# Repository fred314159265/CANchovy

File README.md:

# CANchovy USB-CAN Interface

This repository contains the design file for an isolated USB-CAN interface PCB. It is based upon the MKS CANable V2.0 and is compatible with the [CANable V2.0 firmware](https://github.com/normaldotcom/canable2-fw). It connects to the CAN bus via RJ45 connectors which can be configured with whatever pinout you require!

## Features

* Firmware compatible with [CANable V2.0 firmware](https://github.com/normaldotcom/canable2-fw) - can be flashed & updated with the [CANable 2.0 web updater](https://canable.io/updater/canable2.html).
* RJ45 pinout configured via solder-able jumpers.
* Galvanic isolation between CAN port and USB.
* Two RJ45 connector in parallel allows for inserting inline on bus - all eight signal are passed through.
* DIP switch to enable or disable CAN termination.
* DIP switch to enable silent mode, preventing the CANchovy from transmitting on the bus in hardware.
* JLCPCB basic parts used where possible and all parts available for JLCPCB assembly service. Five CANchovies fully assembled with postage costs around $20 per CANchovy.
* 3D printed case design files.

# Status

Assembled CANchovies from JLCPCB of both revision A & B have been tested and work correctly. The only issues with these version were silkscreen issues.

Revision C has the silkscreen fixed and is ready to manufacture and use.

# Firmware

As the CANchovy is based upon the MKS CANable V2.0, it is compatible with firmware which is compatible with the MKS CANable V2.0.

There area couple of suitable firmware options - which firmware you will want to use really depends on your use case. 

## gs_usb

Using a firmware version which uses the gs_usb protocol will mostly be useful for SocketCAN on Linux, but [python-can](https://python-can.readthedocs.io/en/stable/interfaces/gs_usb.html) does support the gs_usb protocol on all platforms. (__Note:__ The Linux kernel only supports CAN FD with the gs_usb driver after version 5.18.)

* budgetcan_fw - [board_canablev2](https://github.com/ryedwards/budgetcan_fw/tree/main/Portable/board_canablev2) target - I have confirmed that FD CAN is working as of [`e8fb8efebdac22019dc7e73dfec773c6fd2ec5a8`](https://github.com/ryedwards/budgetcan-fw/commit/e8fb8efebdac22019dc7e73dfec773c6fd2ec5a8).
* candlelight build from [CANable 2.0 web updater](https://canable.io/updater/canable2.html) - I have not tested if FD CAN support is present, notes on canable website suggest FD support is not implemented in these candlelight FW builds (yet?).

## SLCAN

SLCAN is a protocol which operates over a serial port. Nearly all OS's have support for serial ports and so is very cross-platform. However, support for SLCAN is not very widespread.

You can also mount the serial port as a SocketCAN port on Linux (E.g. as described [here](https://elinux.org/Bringing_CAN_interface_up).), however, it does not support FD CAN at this time.

FD CAN is possible with the SLCAN firmware, but even fewer programs support FD with SLCAN (if any?). It may be a viable for custom applications where non-Linux is a requirement and Python is not an option.

* slcan with FD support build from [CANable 2.0 web updater](https://canable.io/updater/canable2.html) - [source repo](https://github.com/normaldotcom/canable2-fw).

# Configuring RJ45 Connections

As mentioned above, a feature of this board is that the RJ45's pinout is user configurable. By soldering one jumper for each of the three connections (0V, CAN_H, CAN_L) on the rear of the board, your custom CAN pinout over RJ45 can be supported!

Simply bridge one of the solder jumpers in each of the silkscreen boxes (labelled: 0V, CAN_H & CAN_L) to connect each signal to the corresponding pin number of the RJ45 connectors.

__⚠⚠⚠ Care must be taken to ensure no two signals are connected to the same RJ45 pin! ⚠⚠⚠__

# Ordering

Gerbers, BOM, etc. can all be found in the [releases](https://github.com/fred314159265/CANchovy/releases) area.

When ordering from JLCPCB, is is suggested to select "JLC04161H-7628" under the controlled impedance option, although the USB run is so short that even non-controlled impedance stack-ups will likely work too.

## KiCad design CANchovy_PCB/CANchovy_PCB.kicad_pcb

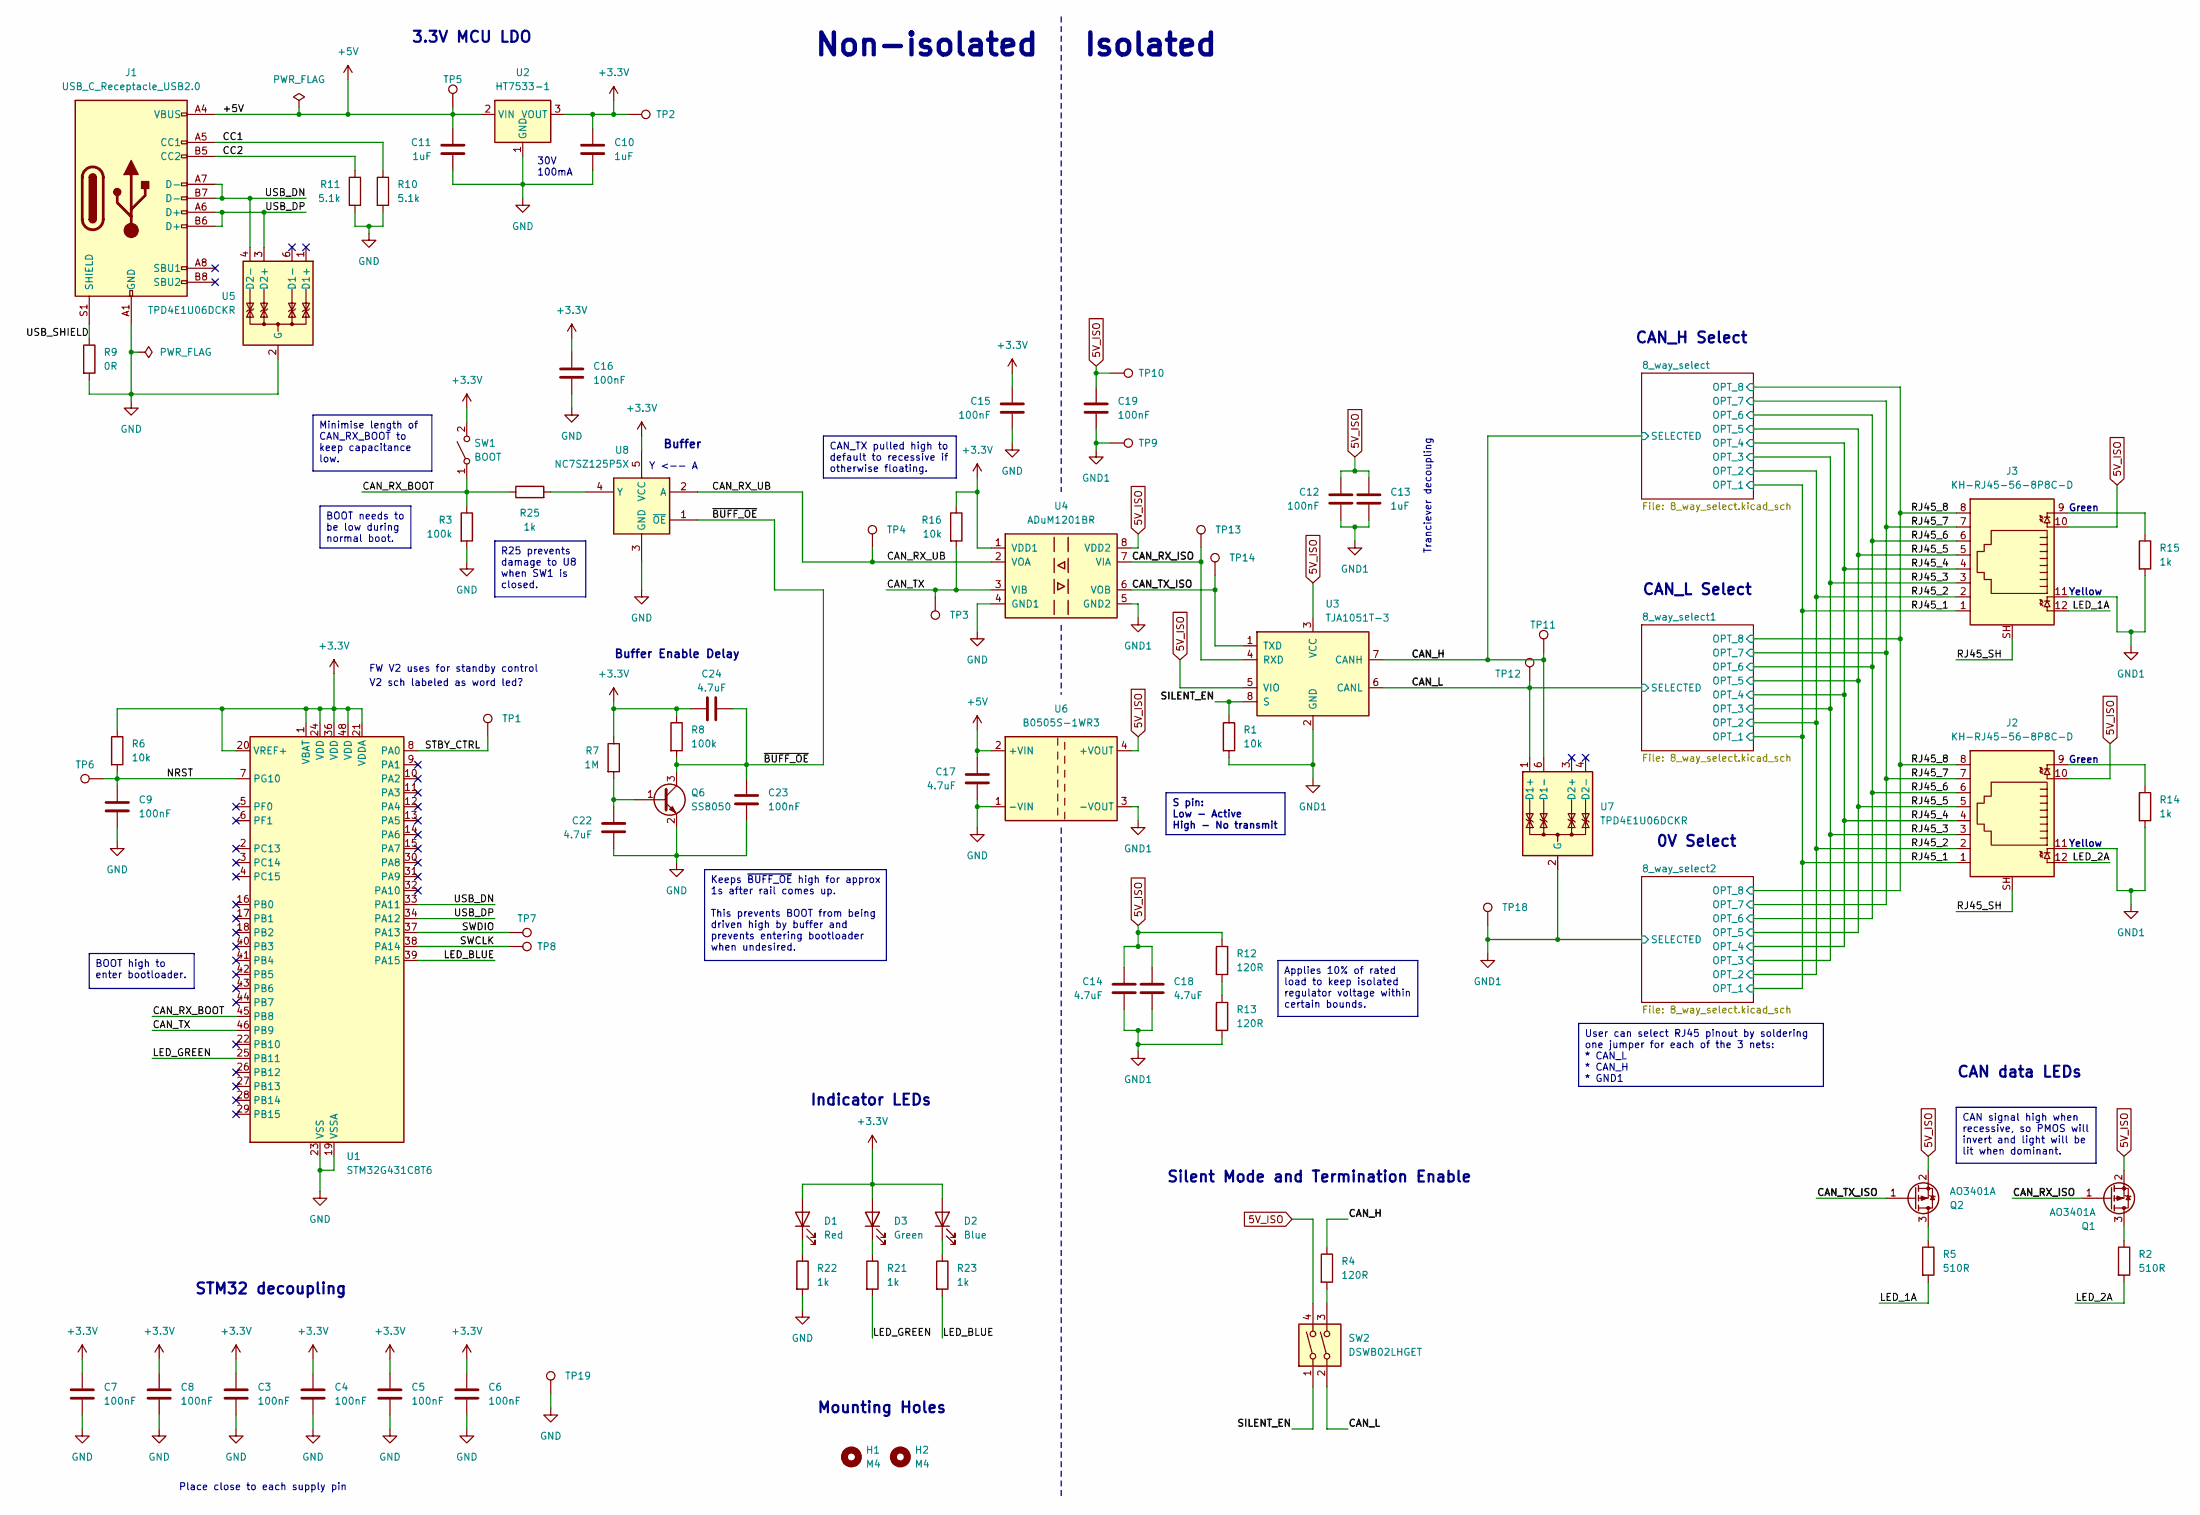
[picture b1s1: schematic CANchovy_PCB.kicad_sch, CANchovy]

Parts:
C3, C4, C5, C6, C7, C8, C9, C12, C15, C16, C19, C23: 100nF; C_0603_1608Metric; Manufacturer Part # CC0603KRX7R9BB104; LCSC Part # C14663
C10, C11, C13: 1uF; C_0805_2012Metric; Manufacturer Part # CL21B105KBFNNNE; LCSC Part # C28323
C14, C17, C18, C22, C24: 4.7uF; C_0805_2012Metric; Manufacturer Part # CL21A475KAQNNNE; LCSC Part # C1779
D1: Red; LED_0603_1608Metric; Manufacturer Part # KT-0603R; LCSC Part # C2286
D2: Blue; LED_0603_1608Metric; Manufacturer Part # XL-1608UBC-04; LCSC Part # C965807
D3: Green; LED_0603_1608Metric; Manufacturer Part # XL-1608UGC-04; LCSC Part # C965804
H1, H2: M4; MountingHole_4.3mm_M4
J1: USB_C_Receptacle_USB2.0; USB_C_Receptacle_XKB_U262-16XN-4BVC11; Manufacturer Part # U262-161N-4BVC11; LCSC Part # C319148
J2, J3: KH-RJ45-56-8P8C-D; Manufacturer Part # KH-RJ45-56-8P8C-D; LCSC Part # C2828082
Q1, Q2: AO3401A; SOT-23; LCSC Part # C15127
Q6: SS8050; SOT-23; Manufacturer Part # SS8050; LCSC Part # C2150
R1, R6, R16: 10k; R_0603_1608Metric; Manufacturer Part # 0603WAF1002T5E; LCSC Part # C25804
R2, R5: 510R; R_0603_1608Metric; Manufacturer Part # 0603WAF5100T5E; LCSC Part # C23193
R3, R8: 100k; R_0603_1608Metric; Manufacturer Part # 0603WAF1003T5E; LCSC Part # C25803
R4, R12, R13: 120R; R_0603_1608Metric; Manufacturer Part # 0603WAF1200T5E; LCSC Part # C22787
R7: 1M; R_0603_1608Metric; Manufacturer Part # 0603WAF1004T5E; LCSC Part # C22935
R9: 0R; R_0603_1608Metric; Manufacturer Part # 0603WAF0000T5E; LCSC Part # C21189
R10, R11: 5.1k; R_0603_1608Metric; Manufacturer Part # 0603WAF5101T5E; LCSC Part # C23186
R14, R15, R21, R22, R23, R25: 1k; R_0603_1608Metric; Manufacturer Part # 0603WAF1001T5E; LCSC Part # C21190
SW1: BOOT; SW_Push_1P1T_XKB_TS-1187A; Manufacturer Part # TS-1187A-B-A-B; LCSC Part # C318884
SW2: DSWB02LHGET; SW_DIP_SPSTx02_Slide_9.78x7.26mm_W7.62mm_P2.54mm; Manufacturer Part # DSWB02LHGET; LCSC Part # C99421
TP1, TP2, TP3, TP4, TP5, TP6, TP7, TP8, TP9, TP10, TP11, TP12, TP13, TP14, TP18, TP19: TestPoint; TestPoint_THTPad_1.0x1.0mm_Drill0.5mm
U1: STM32G431C8T6; LQFP-48_7x7mm_P0.5mm; Manufacturer Part # STM32G431C8T6; LCSC Part # C730096
U2: HT7533-1; SOT-89-3; Manufacturer Part # HT7533-1; LCSC Part # C14289
U3: TJA1051T-3; SOIC-8_3.9x4.9mm_P1.27mm; Manufacturer Part # TJA1051T/3/1J; LCSC Part # C38695
U4: ADuM1201BR; SOIC-8_3.9x4.9mm_P1.27mm; Manufacturer Part # ADUM1201BRZ-RL7; LCSC Part # C87626
U5, U7: TPD4E1U06DCKR; SOT-363_SC-70-6; LCSC Part # C194628
U6: B0505S-1WR3; Converter_DCDC_Murata_CRE1xxxxxx3C_THT; Manufacturer Part # B0505S-1WR3; LCSC Part # C5183119
U8: NC7SZ125P5X; SOT-353_SC-70-5; Manufacturer Part # NC7SZ125P5X; LCSC Part # C112084

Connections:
5V_ISO: C12.1, C13.1, C14.1, C18.1, C19.1, J2.10, J3.10, Q1.2 (S), Q2.2 (S), R12.1, SW2.4, TP10.1, U3.3 (VCC), U3.5 (VIO), U4.8 (VDD2), U6.4 (+VOUT)
+3.3V: C3.1, C4.1, C5.1, C6.1, C7.1, C8.1, C10.1, C15.1, C16.1, C24.1, D1.2 (A), D2.2 (A), D3.2 (A), R6.1, R7.1, R8.1, R16.1, SW1.2 (B), TP2.1, U1.1 (VBAT), U1.20 (VREF+), U1.21 (VDDA), U1.24 (VDD), U1.36 (VDD), U1.48 (VDD), U2.3 (VOUT), U4.1 (VDD1), U8.5 (VCC)
+5V: C11.1, C17.1, J1.A4 (VBUS), J1.A9 (VBUS), J1.B4 (VBUS), J1.B9 (VBUS), TP5.1, U2.2 (VIN), U6.2 (+VIN)
/CAN_H: R4.1, TP11.1, U3.7 (CANH), U7.6 (D1-); also elsewhere on the board
/CAN_L: SW2.2, TP12.1, U3.6 (CANL), U7.1 (D1+); also elsewhere on the board
/CAN_RX_BOOT: R3.1, R25.1, SW1.1 (A), U1.45 (PB8)
/CAN_RX_ISO: Q1.1 (G), TP13.1, U3.4 (RXD), U4.7 (VIA)
/CAN_RX_UB: TP4.1, U4.2 (VOA), U8.2 (A)
/CAN_TX: R16.2, TP3.1, U1.46 (PB9), U4.3 (VIB)
/CAN_TX_ISO: Q2.1 (G), TP14.1, U3.1 (TXD), U4.6 (VOB)
/CC1: J1.A5 (CC1), R10.1
/CC2: J1.B5 (CC2), R11.1
/LED_1A: J3.12, R5.2
/LED_2A: J2.12, R2.2
/LED_BLUE: R23.2, U1.39 (PA15)
/LED_GREEN: R21.2, U1.25 (PB11)
/NRST: C9.1, R6.2, TP6.1, U1.7 (PG10)
/RJ45_1: J2.1, J3.1; also elsewhere on the board
/RJ45_2: J2.2, J3.2; also elsewhere on the board
/RJ45_3: J2.3, J3.3; also elsewhere on the board
/RJ45_4: J2.4, J3.4; also elsewhere on the board
/RJ45_5: J2.5, J3.5; also elsewhere on the board
/RJ45_6: J2.6, J3.6; also elsewhere on the board
/RJ45_7: J2.7, J3.7; also elsewhere on the board
/RJ45_8: J2.8, J3.8; also elsewhere on the board
/RJ45_SH: J2.SH, J3.SH
/SILENT_EN: R1.1, SW2.1, U3.8 (S)
/STBY_CTRL: TP1.1, U1.8 (PA0)
/SWCLK: TP8.1, U1.38 (PA14)
/SWDIO: TP7.1, U1.37 (PA13)
/USB_DN: J1.A7 (D-), J1.B7 (D-), U1.33 (PA11), U5.4 (D2-)
/USB_DP: J1.A6 (D+), J1.B6 (D+), U1.34 (PA12), U5.3 (D2+)
/USB_SHIELD: J1.S1 (SHIELD), R9.1
/~BUFF_OE: C23.1, C24.2, Q6.3 (C), R8.2, U8.1 (~OE)
GND: C3.2, C4.2, C5.2, C6.2, C7.2, C8.2, C9.2, C10.2, C11.2, C15.2, C16.2, C17.2, C22.1, C23.2, J1.A1 (GND), J1.A12 (GND), J1.B1 (GND), J1.B12 (GND), Q6.2 (E), R3.2, R9.2, R10.2, R11.2, R22.2, TP19.1, U1.19 (VSSA), U1.23 (VSS), U1.35 (VSS), U1.47 (VSS), U2.1 (GND), U4.4 (GND1), U5.2 (G), U6.1 (-VIN), U8.3 (GND)
GND1: C12.2, C13.2, C14.2, C18.2, C19.2, J2.11, J3.11, R1.2, R13.2, R14.2, R15.2, TP9.1, TP18.1, U3.2 (GND), U4.5 (GND2), U6.3 (-VOUT), U7.2 (G); also elsewhere on the board
unnamed: D1.1 (K), R22.1
unnamed: D2.1 (K), R23.1
unnamed: D3.1 (K), R21.1
unnamed: J2.9, R14.1
unnamed: J3.9, R15.1
unnamed: Q1.3 (D), R2.1
unnamed: Q2.3 (D), R5.1
unnamed: C22.2, Q6.1 (B), R7.2
unnamed: R4.2, SW2.3
unnamed: R12.2, R13.1
unnamed: R25.2, U8.4 (Y)

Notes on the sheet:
Applies 10% of rated load to keep isolated regulator voltage within certain bounds.
BOOT high to enter bootloader.
BOOT needs to be low during normal boot.
S pin: Low - Active High - No transmit
User can select RJ45 pinout by soldering one jumper for each of the 3 nets: * CAN_L * CAN_H * GND1
Keeps ~{BUFF_OE} high for approx 1s after rail comes up. This prevents BOOT from being driven high by buffer and prevents entering bootloader when undesired.
R25 prevents damage to U8 when SW1 is closed.
CAN signal high when recessive, so PMOS will invert and light will be lit when dominant.
CAN_TX pulled high to default to recessive if otherwise floating.
Minimise length of CAN_RX_BOOT to keep capacitance low.
Mounting Holes
STM32 decoupling
CAN_H Select
Green
Isolated
30V 100mA
Buffer
Y <-- A
Place close to each supply pin
Yellow
Silent Mode and Termination Enable
V2 sch labeled as word led?
Buffer Enable Delay
Non-isolated
3.3V MCU LDO
Tranciever decoupling
0V Select
CAN data LEDs
Indicator LEDs
CAN_L Select
FW V2 uses for standby control

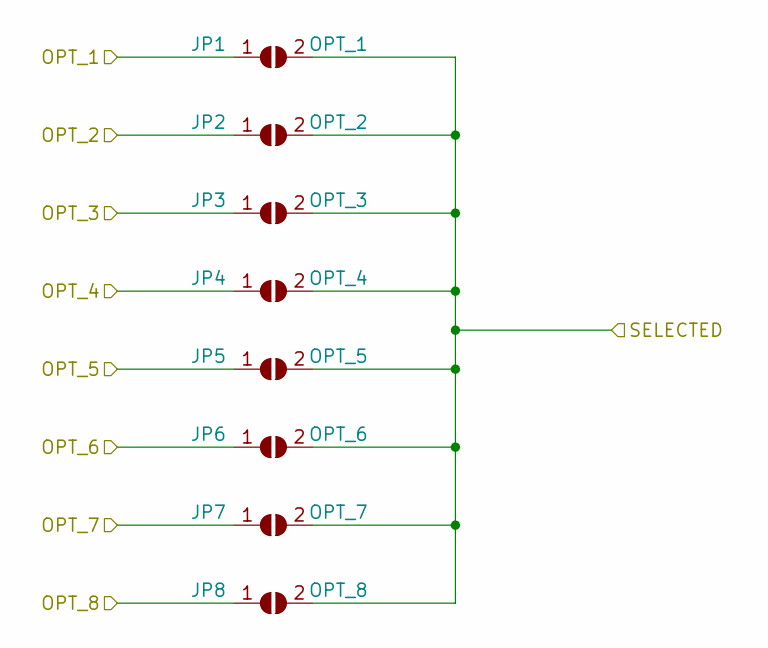
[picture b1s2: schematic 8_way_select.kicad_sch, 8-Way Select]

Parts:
JP1: OPT_1; SolderJumper-2_P1.3mm_Open_TrianglePad1.0x1.5mm
JP2: OPT_2; SolderJumper-2_P1.3mm_Open_TrianglePad1.0x1.5mm
JP3: OPT_3; SolderJumper-2_P1.3mm_Open_TrianglePad1.0x1.5mm
JP4: OPT_4; SolderJumper-2_P1.3mm_Open_TrianglePad1.0x1.5mm
JP5: OPT_5; SolderJumper-2_P1.3mm_Open_TrianglePad1.0x1.5mm
JP6: OPT_6; SolderJumper-2_P1.3mm_Open_TrianglePad1.0x1.5mm
JP7: OPT_7; SolderJumper-2_P1.3mm_Open_TrianglePad1.0x1.5mm
JP8: OPT_8; SolderJumper-2_P1.3mm_Open_TrianglePad1.0x1.5mm

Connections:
/CAN_H: JP1.2 (B), JP2.2 (B), JP3.2 (B), JP4.2 (B), JP5.2 (B), JP6.2 (B), JP7.2 (B), JP8.2 (B); also elsewhere on the board
/RJ45_1: JP1.1 (A); also elsewhere on the board
/RJ45_2: JP2.1 (A); also elsewhere on the board
/RJ45_3: JP3.1 (A); also elsewhere on the board
/RJ45_4: JP4.1 (A); also elsewhere on the board
/RJ45_5: JP5.1 (A); also elsewhere on the board
/RJ45_6: JP6.1 (A); also elsewhere on the board
/RJ45_7: JP7.1 (A); also elsewhere on the board
/RJ45_8: JP8.1 (A); also elsewhere on the board

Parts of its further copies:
JP9, JP17: OPT_1; SolderJumper-2_P1.3mm_Open_TrianglePad1.0x1.5mm
JP10, JP18: OPT_2; SolderJumper-2_P1.3mm_Open_TrianglePad1.0x1.5mm
JP11, JP19: OPT_3; SolderJumper-2_P1.3mm_Open_TrianglePad1.0x1.5mm
JP12, JP20: OPT_4; SolderJumper-2_P1.3mm_Open_TrianglePad1.0x1.5mm
JP13, JP21: OPT_5; SolderJumper-2_P1.3mm_Open_TrianglePad1.0x1.5mm
JP14, JP22: OPT_6; SolderJumper-2_P1.3mm_Open_TrianglePad1.0x1.5mm
JP15, JP23: OPT_7; SolderJumper-2_P1.3mm_Open_TrianglePad1.0x1.5mm
JP16, JP24: OPT_8; SolderJumper-2_P1.3mm_Open_TrianglePad1.0x1.5mm

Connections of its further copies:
/CAN_L: JP9.2 (B), JP10.2 (B), JP11.2 (B), JP12.2 (B), JP13.2 (B), JP14.2 (B), JP15.2 (B), JP16.2 (B); also elsewhere on the board
/RJ45_1: JP9.1 (A), JP17.1 (A); also elsewhere on the board
/RJ45_2: JP10.1 (A), JP18.1 (A); also elsewhere on the board
/RJ45_3: JP11.1 (A), JP19.1 (A); also elsewhere on the board
/RJ45_4: JP12.1 (A), JP20.1 (A); also elsewhere on the board
/RJ45_5: JP13.1 (A), JP21.1 (A); also elsewhere on the board
/RJ45_6: JP14.1 (A), JP22.1 (A); also elsewhere on the board
/RJ45_7: JP15.1 (A), JP23.1 (A); also elsewhere on the board
/RJ45_8: JP16.1 (A), JP24.1 (A); also elsewhere on the board
GND1: JP17.2 (B), JP18.2 (B), JP19.2 (B), JP20.2 (B), JP21.2 (B), JP22.2 (B), JP23.2 (B), JP24.2 (B); also elsewhere on the board

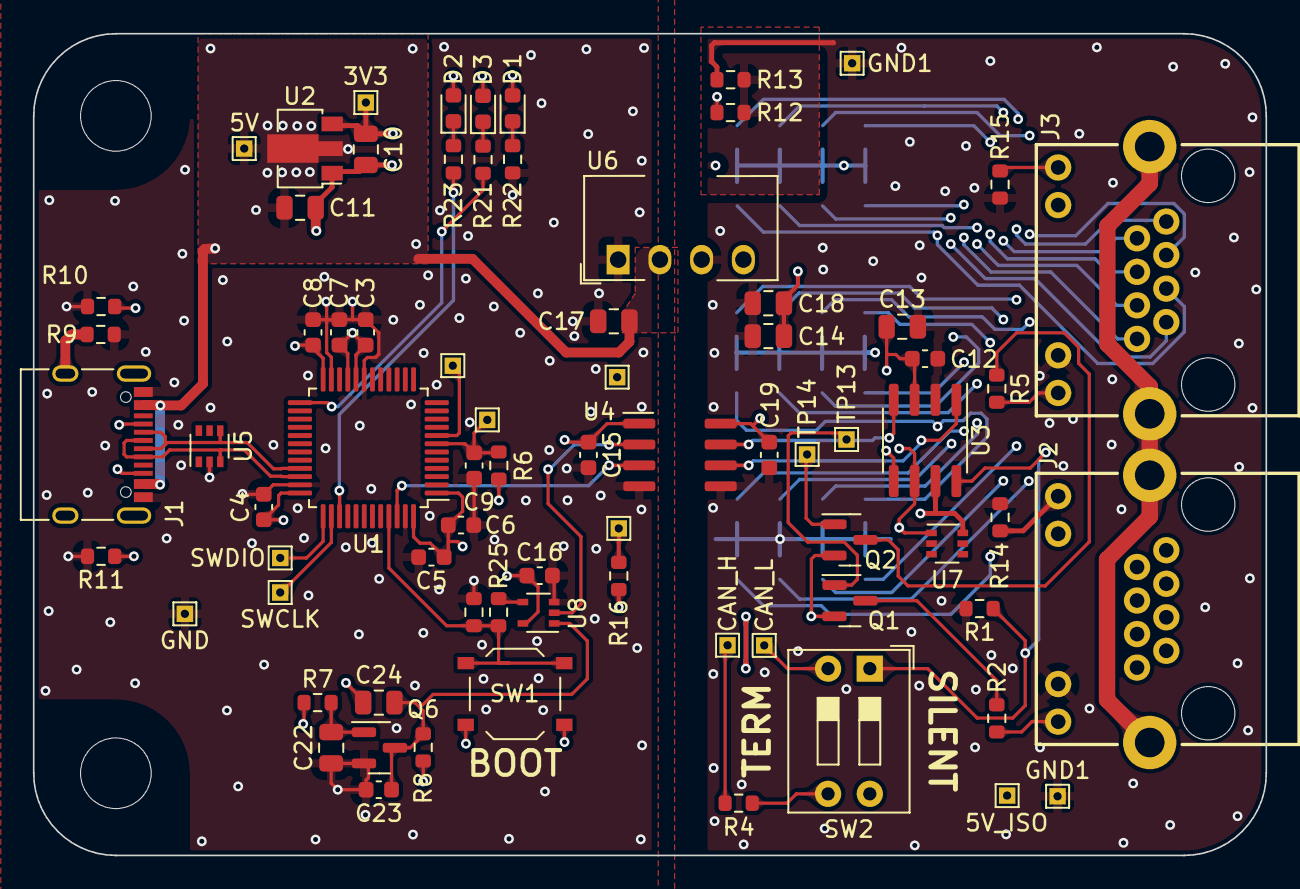
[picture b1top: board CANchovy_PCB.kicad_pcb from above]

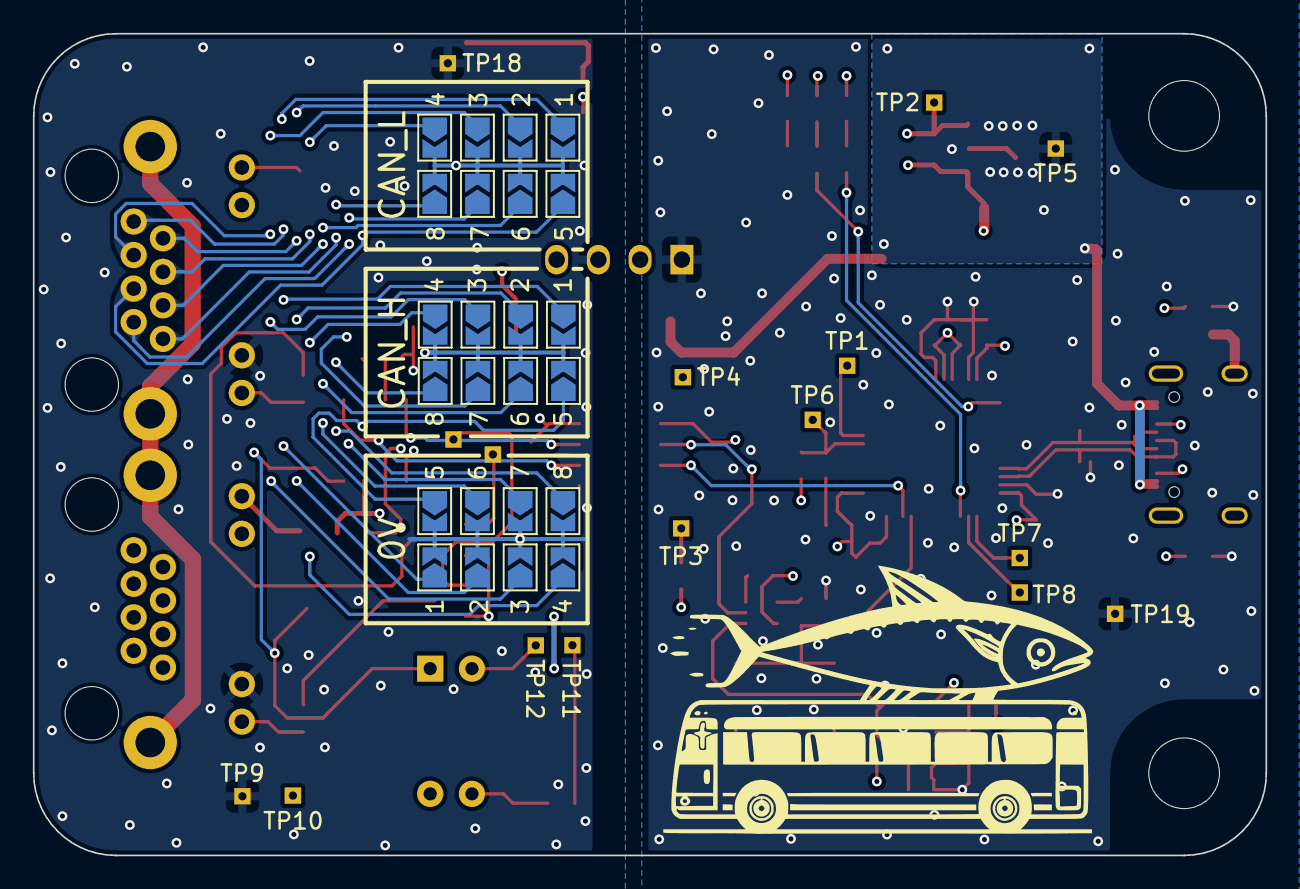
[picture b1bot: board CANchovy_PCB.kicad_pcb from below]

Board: 4 copper layers, 75.0 x 50.0 mm, 101 parts (24 on the bottom side), 47 nets.

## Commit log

2023-10-07 Schematics starting to take shape.
2023-10-13 Schematic pretty much done.
    Could do with a tidy though...
2023-10-16 Isolated side of layout in progress.
2023-10-23 Layout complete for now.
2023-10-31 CANchovy Rev A release.
2023-11-14 First go at case WIP
2023-11-15 Corrected RJ45 footprint pinout and updated PCB to correctly label solder jumpers.
2023-11-15 Added a README
2023-11-15 Renamed KiCAD things to "CANchovy_PCB".
2023-11-16 Revision B release.
    Changes:
    - Silkscreen numbering corrected for RJ45 numberings.
    - RJ45 LEDs for RX/TX now ~twice the current.
2023-11-16 Making some progress on 3DP case.
2023-11-19 MVP 3DP case complete.
2023-11-30 Revision C & readme updates.
2023-12-01 Case tweaks.
2024-04-06 Added some notes on FW options in README.
2024-04-06 Missing URL README.
2024-04-18 Release V1.0
    Green LED D3 changed to C965804.
    Blue LED D2 changed to C965807.
    README edits.
    Design files updated to KiCAD V8 format.
2024-09-06 Updated README to reference "known good" budgetcan commit.
